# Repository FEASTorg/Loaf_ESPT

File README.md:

# Loaf ESPT

ESP32 Thing Plus controller Loaf for building a BREAD from compatible Slices.

## Introduction

This Loaf serves as the supervisory controller and interconnect for one or more Slices. The design includes bus connectors, an ESP32 Thing Plus, a 12V to 5V regulator, 3.3V to 5V logic level shifting, and I2C level shifting and acceleration.

## Usage

[Explain how to use the project. Include examples and screenshots if applicable.]

## Documentation

Please refer to the [docs](/docs) for more info.

---

<div align="center">
  
</div>

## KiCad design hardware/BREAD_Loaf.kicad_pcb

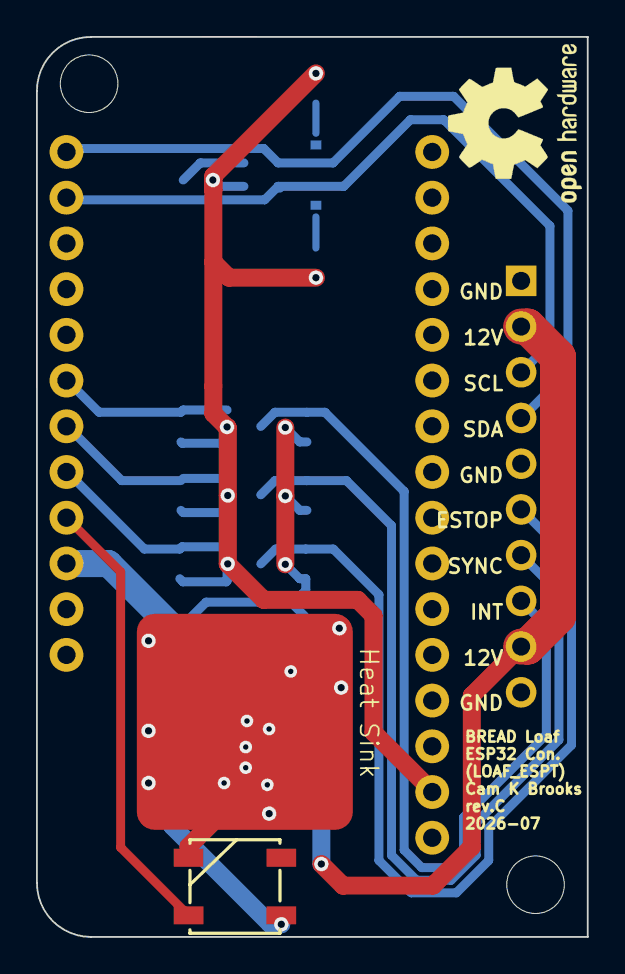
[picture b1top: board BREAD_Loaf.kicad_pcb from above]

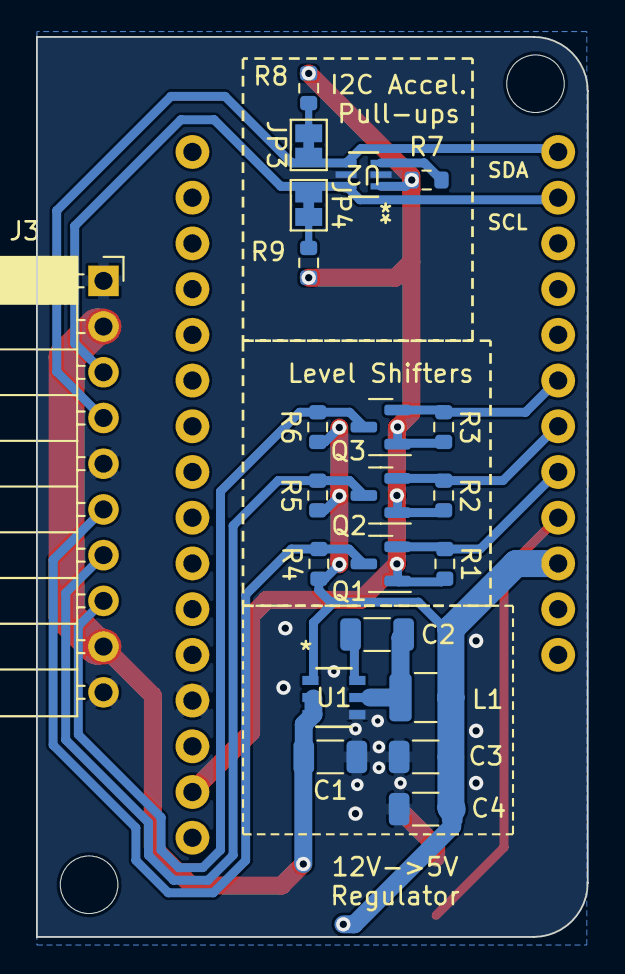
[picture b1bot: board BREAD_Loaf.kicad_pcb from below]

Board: 2 copper layers, 30.6 x 50.0 mm, 27 parts (22 on the bottom side), 18 nets.

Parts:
C1, C3, C4: 22uF; C_1206_3216Metric
C2: 100nF; C_1206_3216Metric
D1: WS2812B_5050; WS2812-5050-4PIN
H1, H2: MountingHole; MountingHole_3.2mm_M3
HS1: Heatsink_Pad; Thermal_Pad
J3: Conn_01x10_Socket; PinSocket_1x10_P2.54mm_Horizontal
JP3, JP4: SolderJumper_2_Bridged; SolderJumper-2_P1.3mm_Bridged_Pad1.0x1.5mm
L1: 4.7uH; L_1210_3225Metric
Q1, Q2, Q3: BSS138; SOT-23
R1, R2, R3, R4, R5, R6, R7: 10k; R_0603_1608Metric
R8, R9: 2.2k; R_0603_1608Metric
U1: AP63205WU-7; SOIC_05WU-7_DIO
U2: LTC4311ISC6-TRMPBF; SOT-6_SC_LIT
U3: ThingPlus; ThingPlus_With_Connectors

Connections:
+3.3V: Q1.1 (G), Q2.1 (G), Q3.1 (G), R1.2, R2.2, R3.2, R7.1, R8.1, R9.1, U2.1 (VCC), U3.27 (3.3V)
+5V: C3.2, C4.2, D1.1 (VDD), L1.2, R4.2, R5.2, R6.2, U1.1 (FB), U3.10 (V_USB)
+12V: C1.2, J3.2, J3.9, U1.2 (EN), U1.3 (VIN)
/E_STOP_3.3V: Q1.2 (S), R1.1, U3.8 (GPIO1)
/E_STOP_5V: J3.6, Q1.3 (D), R4.1
/INT_3.3V: Q2.2 (S), R2.1, U3.7 (GPIO2)
/INT_5V: J3.7, Q2.3 (D), R5.1
/LED_3.3V: D1.4 (DIN), U3.9 (GPIO0)
/SCL_3.3V: J3.3, JP4.1 (A), U2.6 (BUS1), U3.2 (SCL)
/SDA_3.3V: J3.4, JP3.1 (A), U2.4 (BUS2), U3.1 (SDA)
/SYNC_3.3V: Q3.2 (S), R3.1, U3.6 (GPIO3)
/SYNC_5V: J3.8, Q3.3 (D), R6.1
GND: C1.1, C3.1, C4.1, D1.3 (VSS), HS1.1, J3.1, J3.5, J3.10, U1.4 (GND), U2.2 (GND), U2.5 (GND), U3.25 (GND)
unnamed: JP3.2 (B), R8.2
unnamed: JP4.2 (B), R9.2
unnamed: C2.2, U1.6 (BST)
unnamed: C2.1, L1.1, U1.5 (SW)
unnamed: R7.2, U2.3 (ENABLE)

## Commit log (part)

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2024-08-30 updated outputs for fab
2024-08-30 minor changes
2024-08-30 added docs readme for adding documentation on espt loaf
2024-08-31 added art and cleared erc errors
2024-09-10 clean up and set
2024-09-27 updated to remove i2c shifter and optimized layout
2024-09-27 updated tweaks to new version
2024-09-30 JLCPCB order rev-A
